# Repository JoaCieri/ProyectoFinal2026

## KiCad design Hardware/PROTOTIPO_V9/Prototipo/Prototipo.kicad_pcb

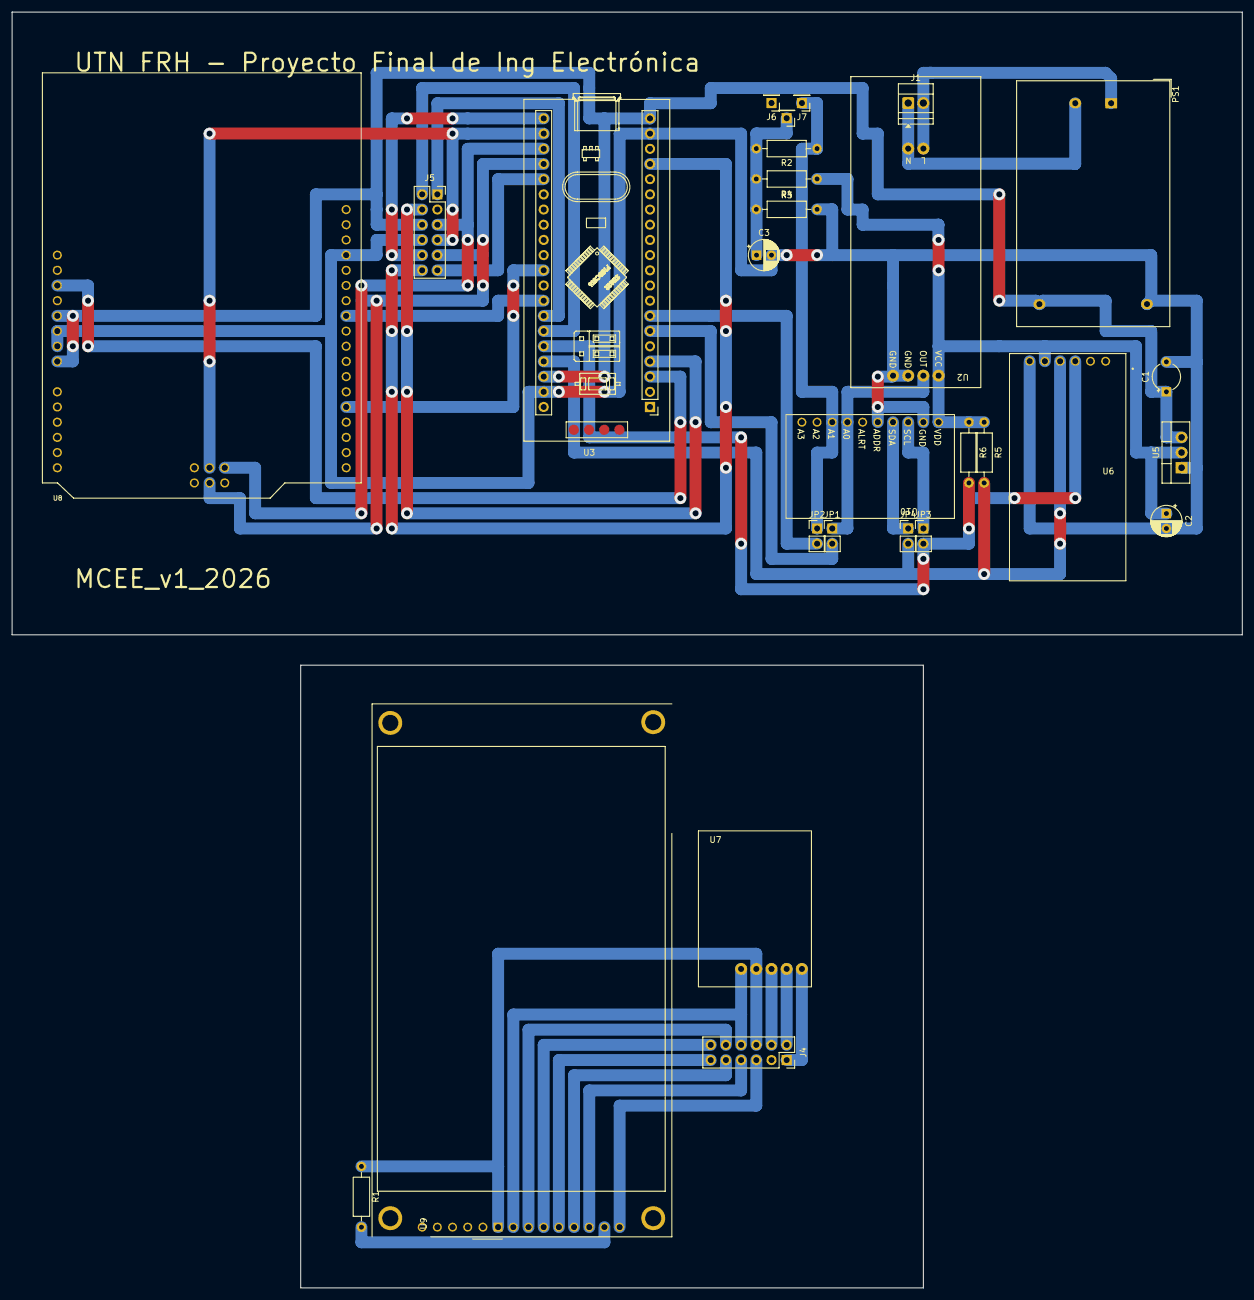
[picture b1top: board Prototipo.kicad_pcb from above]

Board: 2 copper layers, 205.7 x 104.1 mm, 28 parts (0 on the bottom side), 38 nets.

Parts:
C1: 100n; CP_Radial_Tantal_D4.5mm_P5.00mm
C2, C3: 10u; CP_Radial_D5.0mm_P2.50mm
J1: Screw_Terminal_01x02; TerminalBlock_Xinya_XY308-2.54-2P_1x02_P2.54mm_Horizontal
J4, J5: Conn_02x06_Counter_Clockwise; PinSocket_2x06_P2.54mm_Vertical
J6, J7, J8: Conn_01x01; PinHeader_1x01_P2.54mm_Vertical
JP1, JP2, JP3, JP4: Jumper_2_Bridged; PinHeader_1x02_P2.54mm_Vertical
PS1: HLK-5M05; Converter_ACDC_Hi-Link_HLK-5Mxx
R1, R2: 100; R_Axial_DIN0207_L6.3mm_D2.5mm_P10.16mm_Horizontal
R3: 10K; R_Axial_DIN0207_L6.3mm_D2.5mm_P10.16mm_Horizontal
R4: 10k; R_Axial_DIN0207_L6.3mm_D2.5mm_P10.16mm_Horizontal
R5, R6: 1K5; R_Axial_DIN0207_L6.3mm_D2.5mm_P10.16mm_Horizontal
U2: zmpt101b; MODULE_ZMPT101B
U3: YAAJ_BlackPill_Part_Like_SWD_Breakout; YAAJ_BlackPill_SWD_1
U5: LD1117V33; TO-220-3_Vertical
U6: 3013; MODULE_3013
U7: KY-040; MODULE_KY-040
U8: W5500_ETHERNET_SHIELD
U9: CR2013-MI2120
U10: ADS1115IDGS; MODULE_ADS1115

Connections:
+3V3: C2.1, R4.1, R5.1, R6.1, U2.5 (VCC), U5.2 (VO), U6.1 (3.3V), U10.8 (VDD)
+5V: C1.1, J5.6 (Pin_10), PS1.4 (+Vout), U3.20 (5V), U3.38 (5V), U5.3 (VI), U8.5 (5V), U8.8 (VIN)
/ADS1115/ADC_SCL: JP3.1 (A), U10.10 (SCL)
/ADS1115/ADC_SDA: JP4.1 (A), U10.9 (SDA)
/DS3231/RTC_SCL: JP3.2 (B), R6.2, U3.36 (PB8), U6.3 (SCL)
/DS3231/RTC_SDA: JP4.2 (B), R5.2, U3.37 (PB9), U6.4 (SDA)
/PCB2CONNECTION/+5V_: J4.6 (Pin_10), R1.1, U7.VCC, U9.1 (VCC)
/PCB2CONNECTION/BUS_ENC_CLK: J5.1, U3.34 (PB6)
/PCB2CONNECTION/BUS_ENC_DT: J5.2 (Pin_12), U3.35 (PB7)
/PCB2CONNECTION/BUS_ENC_SW: J5.4 (Pin_11), U3.4 (PC15)
/PCB2CONNECTION/BUS_LCD_CS: J5.10 (Pin_8), U3.21 (PB12)
/PCB2CONNECTION/BUS_LCD_DC: J5.11 (Pin_6), U3.25 (PA8)
/PCB2CONNECTION/BUS_LCD_RST: J5.12 (Pin_7), U3.17 (PB10)
/PCB2CONNECTION/ENC_CLK: J4.1, U7.CLK
/PCB2CONNECTION/ENC_DT: J4.2 (Pin_12), U7.DT
/PCB2CONNECTION/ENC_SW: J4.4 (Pin_11), U7.SW
/PCB2CONNECTION/GND_: J4.8 (Pin_9), U7.GND, U9.2 (GND)
/PCB2CONNECTION/LCD_CS: J4.10 (Pin_8), U9.3 (~CS)
/PCB2CONNECTION/LCD_DC: J4.11 (Pin_6), U9.5 (D/~C)
/PCB2CONNECTION/LCD_MISO: J4.5 (Pin_3), U9.9 (MISO)
/PCB2CONNECTION/LCD_MOSI: J4.9 (Pin_5), U9.6 (MOSI)
/PCB2CONNECTION/LCD_RST: J4.12 (Pin_7), U9.4 (RESET)
/PCB2CONNECTION/LCD_SCK: J4.7 (Pin_4), U9.7 (SCK)
/SCT013_100A_1V/RING: C3.1, J8.1, R2.2, R3.1, R4.2
/SCT013_100A_1V/TOP: J7.1, JP2.1 (A), R2.1, U10.5 (AIN1)
/W5500/Eth_CS: U3.33 (PB5), U8.31 (D10)
/W5500/Eth_RST: U3.3 (PC14), U8.3 (RSIN)
/W5500/SD_CS: U3.31 (PB3), U8.25 (D4)
/ZMPT101B/TR_V_1_L: J1.2, PS1.1 (AC/L), U2.1 (L)
/ZMPT101B/TR_V_1_N: J1.1, PS1.2 (AC/N), U2.2 (N)
/ZMPT101B/TR_V_1_OUT: JP1.1 (A), U2.6 (OUT), U10.4 (AIN0)
GND: C1.2, C2.2, C3.2, J5.8 (Pin_9), PS1.3 (-Vout), R3.2, U2.3 (GND), U2.4 (GND), U3.19 (GND), U3.39 (GND), U5.1 (GND), U6.2 (GND), U8.6 (GND1), U8.7 (GND), U8.35 (GND0), U10.1 (ADDR), U10.3 (GND)
MISO: J5.5 (Pin_3), U3.23 (PB14), U8.17 (MISO)
MOSI: J5.9 (Pin_5), U3.24 (PB15), U8.19 (MOSI)
unnamed: JP1.2 (B), U3.6 (PA0)
unnamed: JP2.2 (B), U3.7 (PA1)
unnamed: R1.2, U9.8 (LED)
SCK: J5.7 (Pin_4), U3.22 (PB13), U8.16 (SCL)

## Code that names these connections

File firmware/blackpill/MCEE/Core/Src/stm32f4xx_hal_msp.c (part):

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    __HAL_RCC_GPIOA_CLK_ENABLE();
    __HAL_RCC_GPIOB_CLK_ENABLE();
    /**ADC1 GPIO Configuration
    PA0-WKUP     ------> ADC1_IN0
    PA1     ------> ADC1_IN1
    PA2     ------> ADC1_IN2
    PA3     ------> ADC1_IN3
    PB0     ------> ADC1_IN8
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    __HAL_RCC_ADC1_CLK_DISABLE();

    /**ADC1 GPIO Configuration
    PA0-WKUP     ------> ADC1_IN0
    PA1     ------> ADC1_IN1
    PA2     ------> ADC1_IN2
    PA3     ------> ADC1_IN3
    PB0     ------> ADC1_IN8
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
    __HAL_RCC_GPIOB_CLK_ENABLE();
    /**I2C1 GPIO Configuration
    PB8     ------> I2C1_SCL
    PB9     ------> I2C1_SDA
    */
    GPIO_InitStruct.Pin = GPIO_PIN_8|GPIO_PIN_9;
    GPIO_InitStruct.Mode = GPIO_MODE_AF_OD;
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    __HAL_RCC_I2C1_CLK_DISABLE();

    /**I2C1 GPIO Configuration
    PB8     ------> I2C1_SCL
    PB9     ------> I2C1_SDA
    */
    HAL_GPIO_DeInit(GPIOB, GPIO_PIN_8);

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
    __HAL_RCC_GPIOB_CLK_ENABLE();
    /**SPI2 GPIO Configuration
    PB13     ------> SPI2_SCK
    PB14     ------> SPI2_MISO
    PB15     ------> SPI2_MOSI
    */
    GPIO_InitStruct.Pin = GPIO_PIN_13|GPIO_PIN_14|GPIO_PIN_15;
    GPIO_InitStruct.Mode = GPIO_MODE_AF_PP;
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    __HAL_RCC_SPI2_CLK_DISABLE();

    /**SPI2 GPIO Configuration
    PB13     ------> SPI2_SCK
    PB14     ------> SPI2_MISO
    PB15     ------> SPI2_MOSI
    */
    HAL_GPIO_DeInit(GPIOB, GPIO_PIN_13|GPIO_PIN_14|GPIO_PIN_15);

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
    __HAL_RCC_GPIOB_CLK_ENABLE();
    /**TIM4 GPIO Configuration
    PB6     ------> TIM4_CH1
    PB7     ------> TIM4_CH2
    */
    GPIO_InitStruct.Pin = GPIO_PIN_6|GPIO_PIN_7;
    GPIO_InitStruct.Mode = GPIO_MODE_AF_PP;
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    __HAL_RCC_TIM4_CLK_DISABLE();

    /**TIM4 GPIO Configuration
    PB6     ------> TIM4_CH1
    PB7     ------> TIM4_CH2
    */
    HAL_GPIO_DeInit(GPIOB, GPIO_PIN_6|GPIO_PIN_7);

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
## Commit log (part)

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2026-04-15 First commit
    Directory Tree
    Project structure
    bluepill configuration (clk-pll- 72MHz)
    Firmware initialization
    SD memory Driver
2026-04-15 STM IDE Tutorial
    New file with steps to install enviroment
2026-05-19 GUI modelo Medidas 2
    Se cargan archivos de interfaz grafica de proyecto de medidas 2 como modelo.
2026-05-22 Estructura
2026-05-22 main y driver v1
2026-05-28 CLK TIMER ADC DMA MAIN
    CLK: Configuracion y seteo de PLL, divisores y prescaler.
    TIMER: Configuracion de timer controlador de trigger del ADC.
    ADC: Inicializacion, configuracion de parametros, muestras frecuencia, callbacks.
    DMA: Configuracion de buffer de cola para almacenar por DSP.
    MAIN: Logica para muestrar y calcular tension.

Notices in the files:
firmware/blackpill/MCEE/Core/Src/stm32f4xx_hal_msp.c:
Copyright (c) 2026 STMicroelectronics.
All rights reserved.
This software is licensed under terms that can be found in the LICENSE file
